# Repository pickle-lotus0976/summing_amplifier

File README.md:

# Summing Amplifier

This is a simple summing amplifier project made in KiCad using a TI LMV601 Operational Amplifier. This is my first PCB design.

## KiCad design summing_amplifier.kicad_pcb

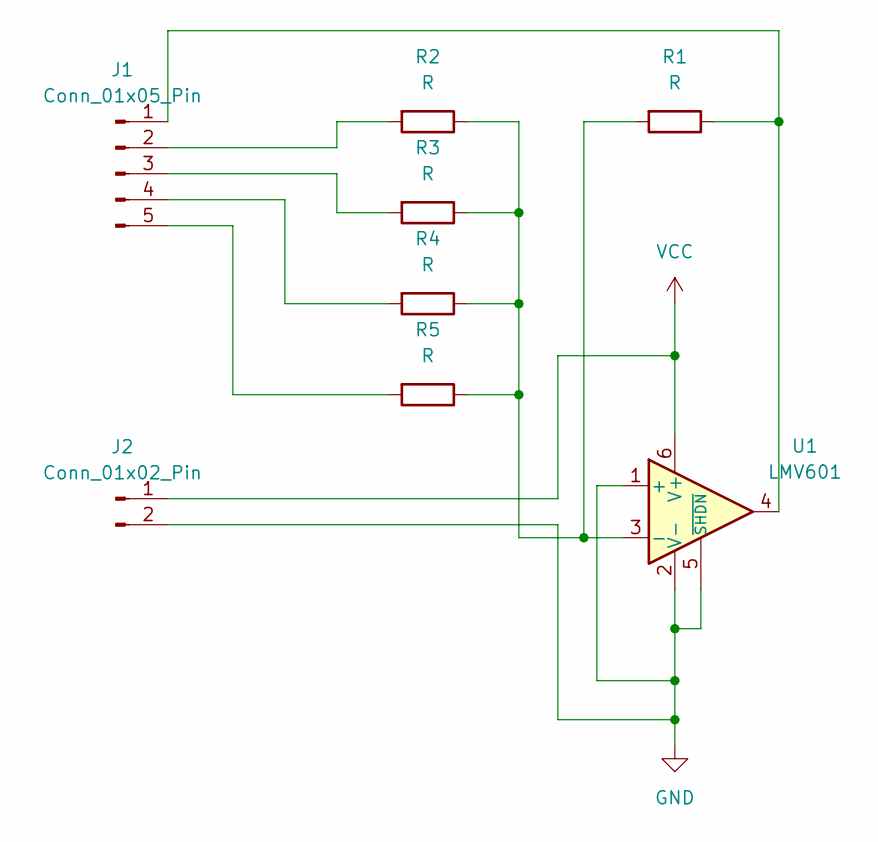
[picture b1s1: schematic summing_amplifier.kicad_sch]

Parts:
J1: Conn_01x05_Pin; TE_826576-5_1x05_P3.96mm_Vertical
J2: Conn_01x02_Pin; TE_826576-2_1x02_P3.96mm_Vertical
R1, R5: R; R_Axial_DIN0204_L3.6mm_D1.6mm_P1.90mm_Vertical
R2, R4: R; R_Axial_DIN0204_L3.6mm_D1.6mm_P2.54mm_Vertical
R3: R; R_Axial_DIN0204_L3.6mm_D1.6mm_P5.08mm_Horizontal
U1: LMV601; SOT-363_SC-70-6

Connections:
GND: J2.2, U1.1 (+), U1.2 (V-), U1.5 (~SHDN)
unnamed: J1.1, R1.1, U1.4
unnamed: J1.2, R2.2
unnamed: J1.3, R3.2
unnamed: J1.4, R4.2
unnamed: J1.5, R5.2
unnamed: R1.2, R2.1, R3.1, R4.1, R5.1, U1.3 (-)
VCC: J2.1, U1.6 (V+)

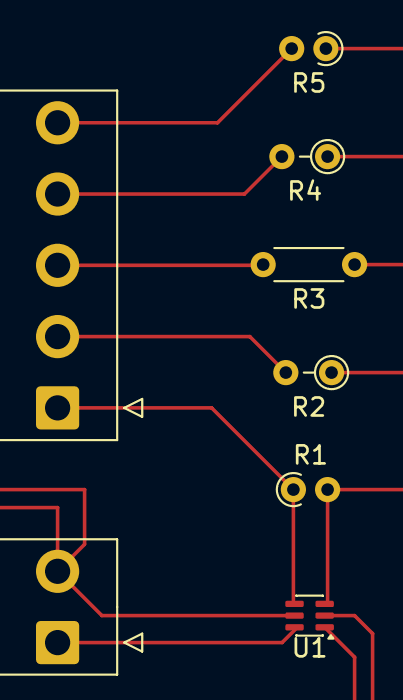
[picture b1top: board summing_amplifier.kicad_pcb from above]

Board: 2 copper layers, 8 parts (0 on the bottom side), 8 nets.
